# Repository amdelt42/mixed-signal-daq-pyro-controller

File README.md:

# Mixed-Signal DAQ & Pyrotechnic Control System

This repository contains the [firmware / hardware design] for an STM32-powered data acquisition board.

## Key Features

* **Microcontroller:** STM32 core managing real-time loops, sensor aggregation, and firing logic.
* **Analog Front End:** 
  * Full-bridge strain gauge and Thermocouple measurement signal blocks with dedicated filtering.
  * Local digital temperature sensor for real-time Cold-Junction Compensation (CJC).
  * High-resolution Analog-to-Digital Converter (ADC).
* **Actuation:** Integrated pyrotechnic firing channels.
* **Telemetry & Comms:** High bit-rate CAN FD transceiver for high-bandwidth data output.

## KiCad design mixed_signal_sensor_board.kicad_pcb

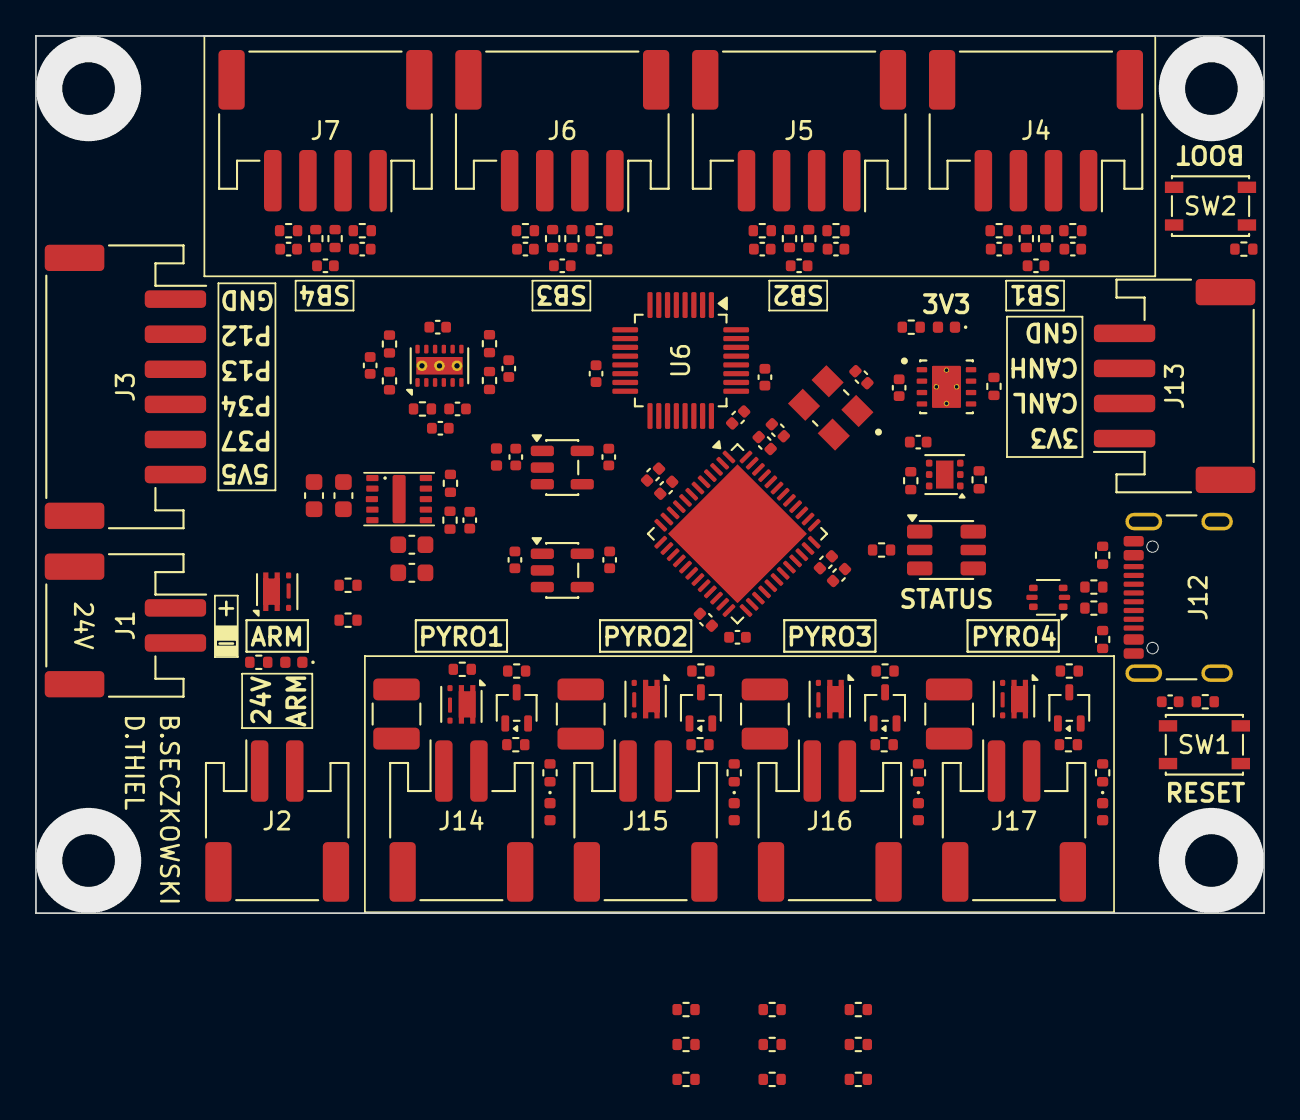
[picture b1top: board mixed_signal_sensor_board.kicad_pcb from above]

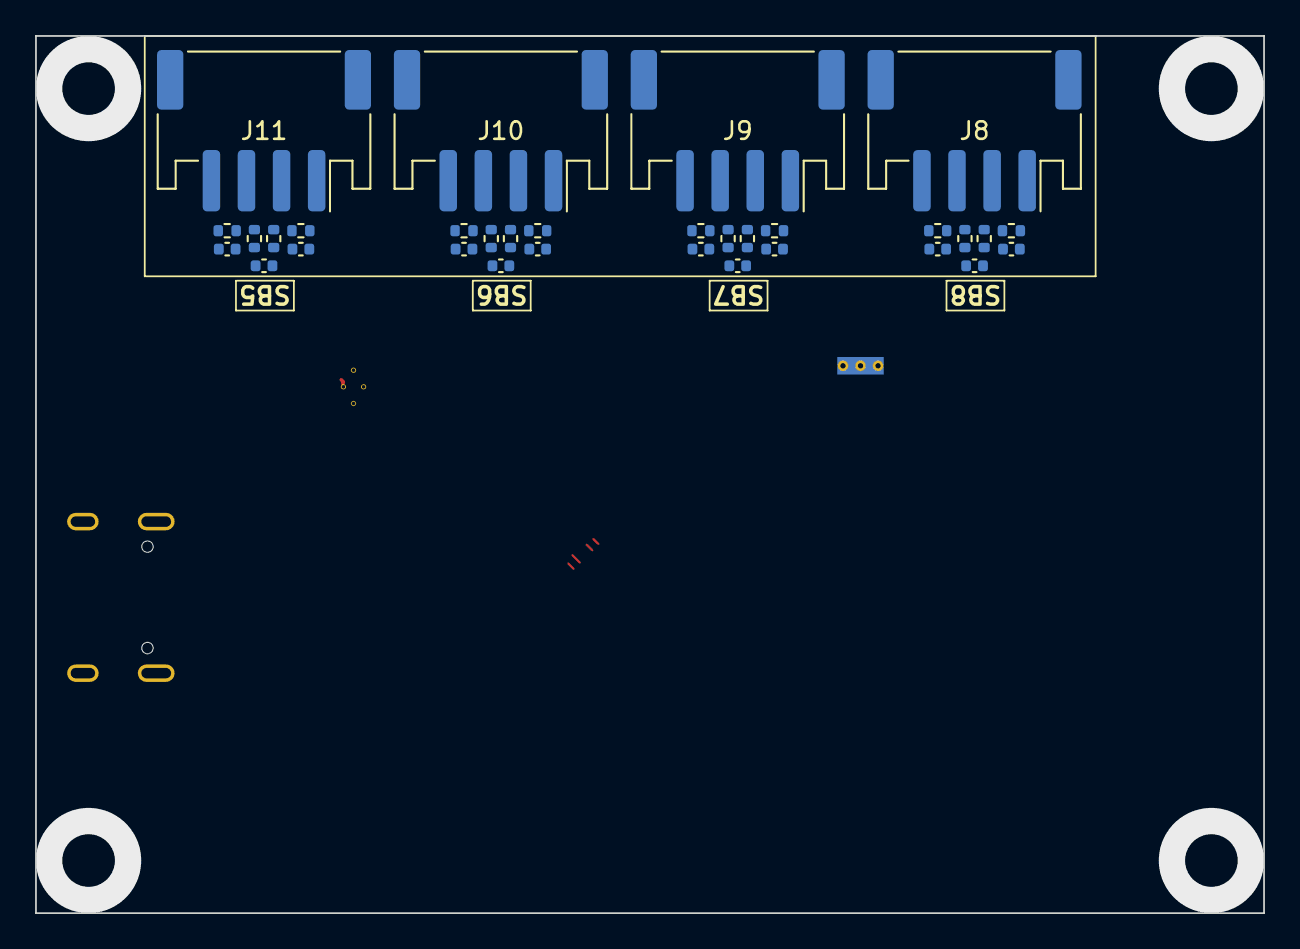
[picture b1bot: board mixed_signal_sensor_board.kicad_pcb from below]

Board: 4 copper layers, 70.0 x 50.0 mm, 178 parts (32 on the bottom side), 111 nets.

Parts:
C1: 4.7uF; C_0603_1608Metric
C2, C6, C21, C22, C23: 4.7uF; C_0402_1005Metric
C3: 0.47uF; C_0402_1005Metric
C4: 0.47uF; C_0603_1608Metric
C5, C14, C18, C19, C20, C28, C30, C31, C33, C34, C36, C37, C39, C40, C42, C43, C45, C46, C48, C49, C51, C52, C53: 0.1uF; C_0402_1005Metric
C7, C8: 10uF; C_0603_1608Metric
C9, C11: 2.2uF; C_0402_1005Metric
C10: 47pf; C_0402_1005Metric
C12, C13, C15, C16, C17, C24, C26: 1uF; C_0402_1005Metric
C25: 0.22uF; C_0402_1005Metric
C27: 10nF; C_0402_1005Metric
C29, C32, C35, C38, C41, C44, C47, C50: 10nf; C_0402_1005Metric
D1: 24V; D_0402_1005Metric
D2: SMLVN6RGB; LED_ROHM_SMLVN6
D3: LED; LED_0402_1005Metric
D4, D5, D6, D7: 3V; D_0402_1005Metric
F1, F2, F3, F4: MF-USHT050KX-2; Fuse_1210_3225Metric
FB1: 600Ω@100MHz; L_0402_1005Metric
J1: Conn_01x02; JST_PH_S2B-PH-SM4-TB_1x02-1MP_P2.00mm_Horizontal
J2: PYRO_ARM; JST_PH_S2B-PH-SM4-TB_1x02-1MP_P2.00mm_Horizontal
J3: Conn_01x06; JST_PH_S6B-PH-SM4-TB_1x06-1MP_P2.00mm_Horizontal
J4, J5, J6, J7, J8, J9, J10, J11, J13: Conn_01x04; JST_PH_S4B-PH-SM4-TB_1x04-1MP_P2.00mm_Horizontal
J12: USB_C_Receptacle_USB2.0_16P; USB_C_Receptacle_GCT_USB4105-xx-A_16P_TopMnt_Horizontal
J14, J15, J16, J17: PYRO; JST_PH_S2B-PH-SM4-TB_1x02-1MP_P2.00mm_Horizontal
Q2, Q4, Q6, Q8: 2N7002WT1G; SOT-323_SC-70
Q3, Q5, Q7, Q9, Q10: SQA405EJ-T1_GE3; Vishay_PowerPAK_SC70-6L_Single
R1, R5, R6, R9, R10, R17, R18, R21, R22, R25, R26, R29, R30, R33, R34, R37, R38, R41, R42, R45, R46: 10K; R_0402_1005Metric
R2, R7: 100K; R_0402_1005Metric
R3, R4: 5K; R_0402_1005Metric
R8: 16K9; R_0402_1005Metric
R11, R14, R51: 120R; R_0402_1005Metric
R12, R13: 4K7; R_0402_1005Metric
R15, R16, R19, R20, R23, R24, R27, R28, R31, R32, R35, R36, R39, R40, R43, R44: 1MΩ; R_0402_1005Metric
R47, R48: 5K1; R_0402_1005Metric
R49, R50: 22R; R_0402_1005Metric
R52, R54, R58, R60, R64, R66, R70, R72: 10k; R_0402_1005Metric
R53, R55, R59, R61, R65, R67, R71, R73: 1k; R_0402_1005Metric
R56, R57, R62, R63, R68, R69, R74, R75: 50k; R_0402_1005Metric
SW1, SW2: SW_Push; SW_SPST_PTS810
U1: TMP117xxDRV; WSON-6-1EP_2x2mm_P0.65mm_EP1x1.6mm
U2: LM27762; WSON-12-1EP_3x2mm_P0.5mm_EP1x2.65_ThermalVias
U3: MagI3C_171013201
U4, U5: TPS7A20xxxDBV; SOT-23-5
U6: ADS131M08xPBS; TQFP-32_5x5mm_P0.5mm
U7: STM32L552CEUx; QFN-48-1EP_7x7mm_P0.5mm_EP5.6x5.6mm
U8: USBLC6-2P6; SOT-666
U9: TCAN3414DRBR; XCVR_TCAN3414DRBR
Y1: SG-8018CE_8.192M-TJHSA; OSC_SG-8018CE_8.9152M-TJHSA0

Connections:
+3V3: C5.1, C16.1, C18.2, C19.2, C20.2, C21.2, C22.2, C23.2, C24.1, C28.2, C53.1, J13.1, R3.2, R4.2, R12.1, R14.1, SW2.1, U1.5 (V+), U5.5 (OUT), U6.26 (DVDD), U7.1 (VBAT), U7.24 (VDD), U7.36 (VDD), U7.48 (VDD), U9.3 (VCC), Y1.1 (~ST), Y1.4 (VCC)
+3V3A: C15.1, C17.1, C26.2, C27.2, R15.1, R19.1, R23.1, R27.1, R31.1, R35.1, R39.1, R43.1, U4.5 (OUT), U6.15 (AVDD), U7.9 (VDDA)
+5V: C9.1, J4.1, J5.1, J6.1, J7.1, J8.1, J9.1, J10.1, J11.1, R5.1, U2.11 (OUT+)
+5V5: C2.2, C7.2, C8.2, C10.2, C13.2, FB1.2, J3.6, R1.1, R7.1, U2.3 (VIN), U2.8 (EN-), U2.12 (EN+), U3.6 (VOUT), U5.1 (IN), U5.3 (EN)
+24V: C1.2, C4.2, D1.1 (K), J2.1, Q10.4 (S), R56.2, R62.2, R68.2, R74.2, U3.3 (VIN), U3.4 (EN)
-5V: C11.1, J4.4, J5.4, J6.4, J7.4, J8.4, J9.4, J10.4, J11.4, R9.1, U2.6 (OUT-)
/ADS_DRDY: U6.18 (~DRDY), U7.2 (PC13)
/ADS_SYNC/RESET: U6.16 (~SYNC/~RESET), U7.3 (PC14)
/BOOT0: R13.1, SW2.2, U7.44 (PH3)
/CAN/CAN_H: J13.3, R51.2, U9.7 (CANH)
/CAN/CAN_L: J13.2, R51.1, U9.6 (CANL)
/CAN_RX: U7.45 (PB8), U9.4 (RXD)
/CAN_TX: U7.46 (PB9), U9.1 (TXD)
/CLK_IN: U6.23 (XTAL1/CLKIN), Y1.3 (OUT)
/CS: U6.17 (~CS), U7.14 (PA4)
/FB: C10.1, R7.2, R8.1, U3.7 (FB)
/FB+: R5.2, R6.1, U2.2 (FB+)
/FB-: R9.2, R10.1, U2.7 (FB-)
/LEDB: D2.1 (BA), U7.41 (PB5)
/LEDG: D2.3 (GA), U7.39 (PB3)
/LEDR: R11.1, U7.40 (PB4)
/MISO: U6.20 (DOUT), U7.16 (PA6)
/MOSI: U6.21 (DIN), U7.17 (PA7)
/NRST: C14.1, R12.2, SW1.2, U7.7 (NRST)
/PGOOD: R1.2, U2.1 (PGOOD), U7.38 (PA15)
/PYRO1_FAULT: D4.1 (K), R57.2, U7.19 (PB1)
/PYRO1_SIGNAL: R52.2, R53.1, U7.18 (PB0)
/PYRO2_FAULT: D5.1 (K), R63.2, U7.21 (PB10)
/PYRO2_SIGNAL: R58.2, R59.1, U7.20 (PB2)
/PYRO3_FAULT: D6.1 (K), R69.2, U7.28 (PB15)
/PYRO3_SIGNAL: R64.2, R65.1, U7.29 (PA8)
/PYRO4_FAULT: D7.1 (K), R75.2, U7.30 (PA9)
/PYRO4_SIGNAL: R70.2, R71.1, U7.31 (PA10)
/SB1/AOUT_N: C29.2, C31.2, R18.2, U6.2 (AIN2N)
/SB1/AOUT_P: C29.1, C30.1, R17.2, U6.1 (AIN2P)
/SB1/SIGNAL_N: J4.3, R16.1, R18.1
/SB1/SIGNAL_P: J4.2, R15.2, R17.1
/SB2/AOUT_N: C32.2, C34.2, R22.2, U6.3 (AIN3N)
/SB2/AOUT_P: C32.1, C33.1, R21.2, U6.4 (AIN3P)
/SB2/SIGNAL_N: J5.3, R20.1, R22.1
/SB2/SIGNAL_P: J5.2, R19.2, R21.1
/SB3/AOUT_N: C35.2, C37.2, R26.2, U6.6 (AIN4N)
/SB3/AOUT_P: C35.1, C36.1, R25.2, U6.5 (AIN4P)
/SB3/SIGNAL_N: J6.3, R24.1, R26.1
/SB3/SIGNAL_P: J6.2, R23.2, R25.1
/SB4/AOUT_N: C38.2, C40.2, R30.2, U6.7 (AIN5N)
/SB4/AOUT_P: C38.1, C39.1, R29.2, U6.8 (AIN5P)
/SB4/SIGNAL_N: J7.3, R28.1, R30.1
/SB4/SIGNAL_P: J7.2, R27.2, R29.1
/SB5/AOUT_N: C41.2, C43.2, R34.2, U6.11 (AIN7N)
/SB5/AOUT_P: C41.1, C42.1, R33.2, U6.12 (AIN7P)
/SB5/SIGNAL_N: J8.3, R32.1, R34.1
/SB5/SIGNAL_P: J8.2, R31.2, R33.1
/SB6/AOUT_N: C44.2, C46.2, R38.2, U6.10 (AIN6N)
/SB6/AOUT_P: C44.1, C45.1, R37.2, U6.9 (AIN6P)
/SB6/SIGNAL_N: J9.3, R36.1, R38.1
/SB6/SIGNAL_P: J9.2, R35.2, R37.1
/SB7/AOUT_N: C47.2, C49.2, R42.2, U6.31 (AIN1N)
/SB7/AOUT_P: C47.1, C48.1, R41.2, U6.32 (AIN1P)
/SB7/SIGNAL_N: J10.3, R40.1, R42.1
/SB7/SIGNAL_P: J10.2, R39.2, R41.1
/SB8/AOUT_N: C50.2, C52.2, R46.2, U6.30 (AIN0N)
/SB8/AOUT_P: C50.1, C51.1, R45.2, U6.29 (AIN0P)
/SB8/SIGNAL_N: J11.3, R44.1, R46.1
/SB8/SIGNAL_P: J11.2, R43.2, R45.1
/SCL: R4.1, U1.1 (SCL), U7.42 (PB6)
/SCLK: U6.19 (SCLK), U7.15 (PA5)
/SDA: R3.1, U1.6 (SDA), U7.43 (PB7)
/SWCLK: J3.5, U7.37 (PA14)
/SWDIO: J3.4, U7.34 (PA13)
/USART2_RX: J3.3, U7.13 (PA3)
/USART2_TX: J3.2, U7.12 (PA2)
/USB/DN: J12.A7 (D-), J12.B7 (D-), R49.1
/USB/DP: J12.A6 (D+), J12.B6 (D+), R50.1
/USB_N: U7.32 (PA11), U8.6 (I/O1)
/USB_P: U7.33 (PA12), U8.4 (I/O2)
ARM: J2.2, Q3.1 (D), Q5.1 (D), Q7.1 (D), Q9.1 (D), R54.1, R60.1, R66.1, R72.1
GND: C1.1, C2.1, C4.1, C5.2, C6.2, C7.1, C8.1, C9.2, C11.2, C12.1, C13.1, C14.2, C15.2, C16.2, C17.2, C18.1, C19.1, C20.1, C21.1, C22.1, C23.1, C24.2, C25.2, C26.1, C27.1, C28.1, C30.2, C31.1, C33.2, C34.1, C36.2, C37.1, C39.2, C40.1, C42.2, C43.1, C45.2, C46.1, C48.2, C49.1, C51.2, C52.1, C53.2, D2.4 (GK), D2.5 (RK), D2.6 (BK), D3.1 (K), D4.2 (A), D5.2 (A), D6.2 (A), D7.2 (A), J1.2, J3.1, J12.A1 (GND), J12.A12 (GND), J12.B1 (GND), J12.B12 (GND), J13.4, J14.2, J15.2, J16.2, J17.2, Q2.2 (S), Q4.2 (S), Q6.2 (S), Q8.2 (S), R2.2, R6.2, R8.2, R10.2, R13.2, R16.2, R20.2, R24.2, R28.2, R32.2, R36.2, R40.2, R44.2, R47.1, R48.1, R52.1, R58.1, R64.1, R70.1, SW1.1, U1.2 (GND), U1.4 (ADD0), U2.4 (GND), U2.13 (PAD), U3.1 (GND), U4.2 (GND), U5.2 (GND), U6.13 (AGND), U6.25 (DGND), U6.27 (AGND), U6.28 (AGND), U7.8 (VSSA), U7.23 (VSS), U7.35 (VSS), U7.47 (VSS), U7.49 (VSS), U8.2 (GND), U9.2 (GND), U9.5 (SHDN), U9.8 (STB), U9.9 (EXP), Y1.2 (GND)
unnamed: D1.2 (A), Q10.3 (G), R2.1
unnamed: D2.2 (RA), R11.2
unnamed: D3.2 (A), R14.2
unnamed: J1.1, Q10.1 (D)
unnamed: J12.A5 (CC1), R48.2
unnamed: J12.B5 (CC2), R47.2
unnamed: F1.2, J14.1, R56.1, R57.1
unnamed: F2.2, J15.1, R62.1, R63.1
unnamed: F3.2, J16.1, R68.1, R69.1
unnamed: F4.2, J17.1, R74.1, R75.1
unnamed: Q2.3 (D), R54.2, R55.1
unnamed: Q2.1 (G), R53.2
unnamed: Q3.3 (G), R55.2
unnamed: F1.1, Q3.4 (S)
unnamed: Q4.3 (D), R60.2, R61.1
unnamed: Q4.1 (G), R59.2
unnamed: Q5.3 (G), R61.2
unnamed: F2.1, Q5.4 (S)
unnamed: Q6.3 (D), R66.2, R67.1
unnamed: Q6.1 (G), R65.2
unnamed: Q7.3 (G), R67.2
unnamed: F3.1, Q7.4 (S)
unnamed: Q8.3 (D), R72.2, R73.1
unnamed: Q8.1 (G), R71.2
unnamed: Q9.3 (G), R73.2
unnamed: F4.1, Q9.4 (S)
unnamed: R49.2, U8.1 (I/O1)
unnamed: R50.2, U8.3 (I/O2)
unnamed: C3.1, U2.10 (C+)
unnamed: C3.2, U2.9 (C-)
unnamed: C6.1, U2.5 (CP)
unnamed: C12.2, FB1.1, U4.1 (IN), U4.3 (EN)
unnamed: C25.1, U6.24 (CAP)
